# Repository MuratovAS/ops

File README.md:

# ops
Open pocket switch

Very raw work is stored here. Don't use it!
Everything needs to be redone.
Problems:
- routes are not coordinated
- technological standards are not observed

https://wiki.pine64.org/wiki/Clusterboard
https://github.com/libc0607/Realtek_switch_hacking/tree/files

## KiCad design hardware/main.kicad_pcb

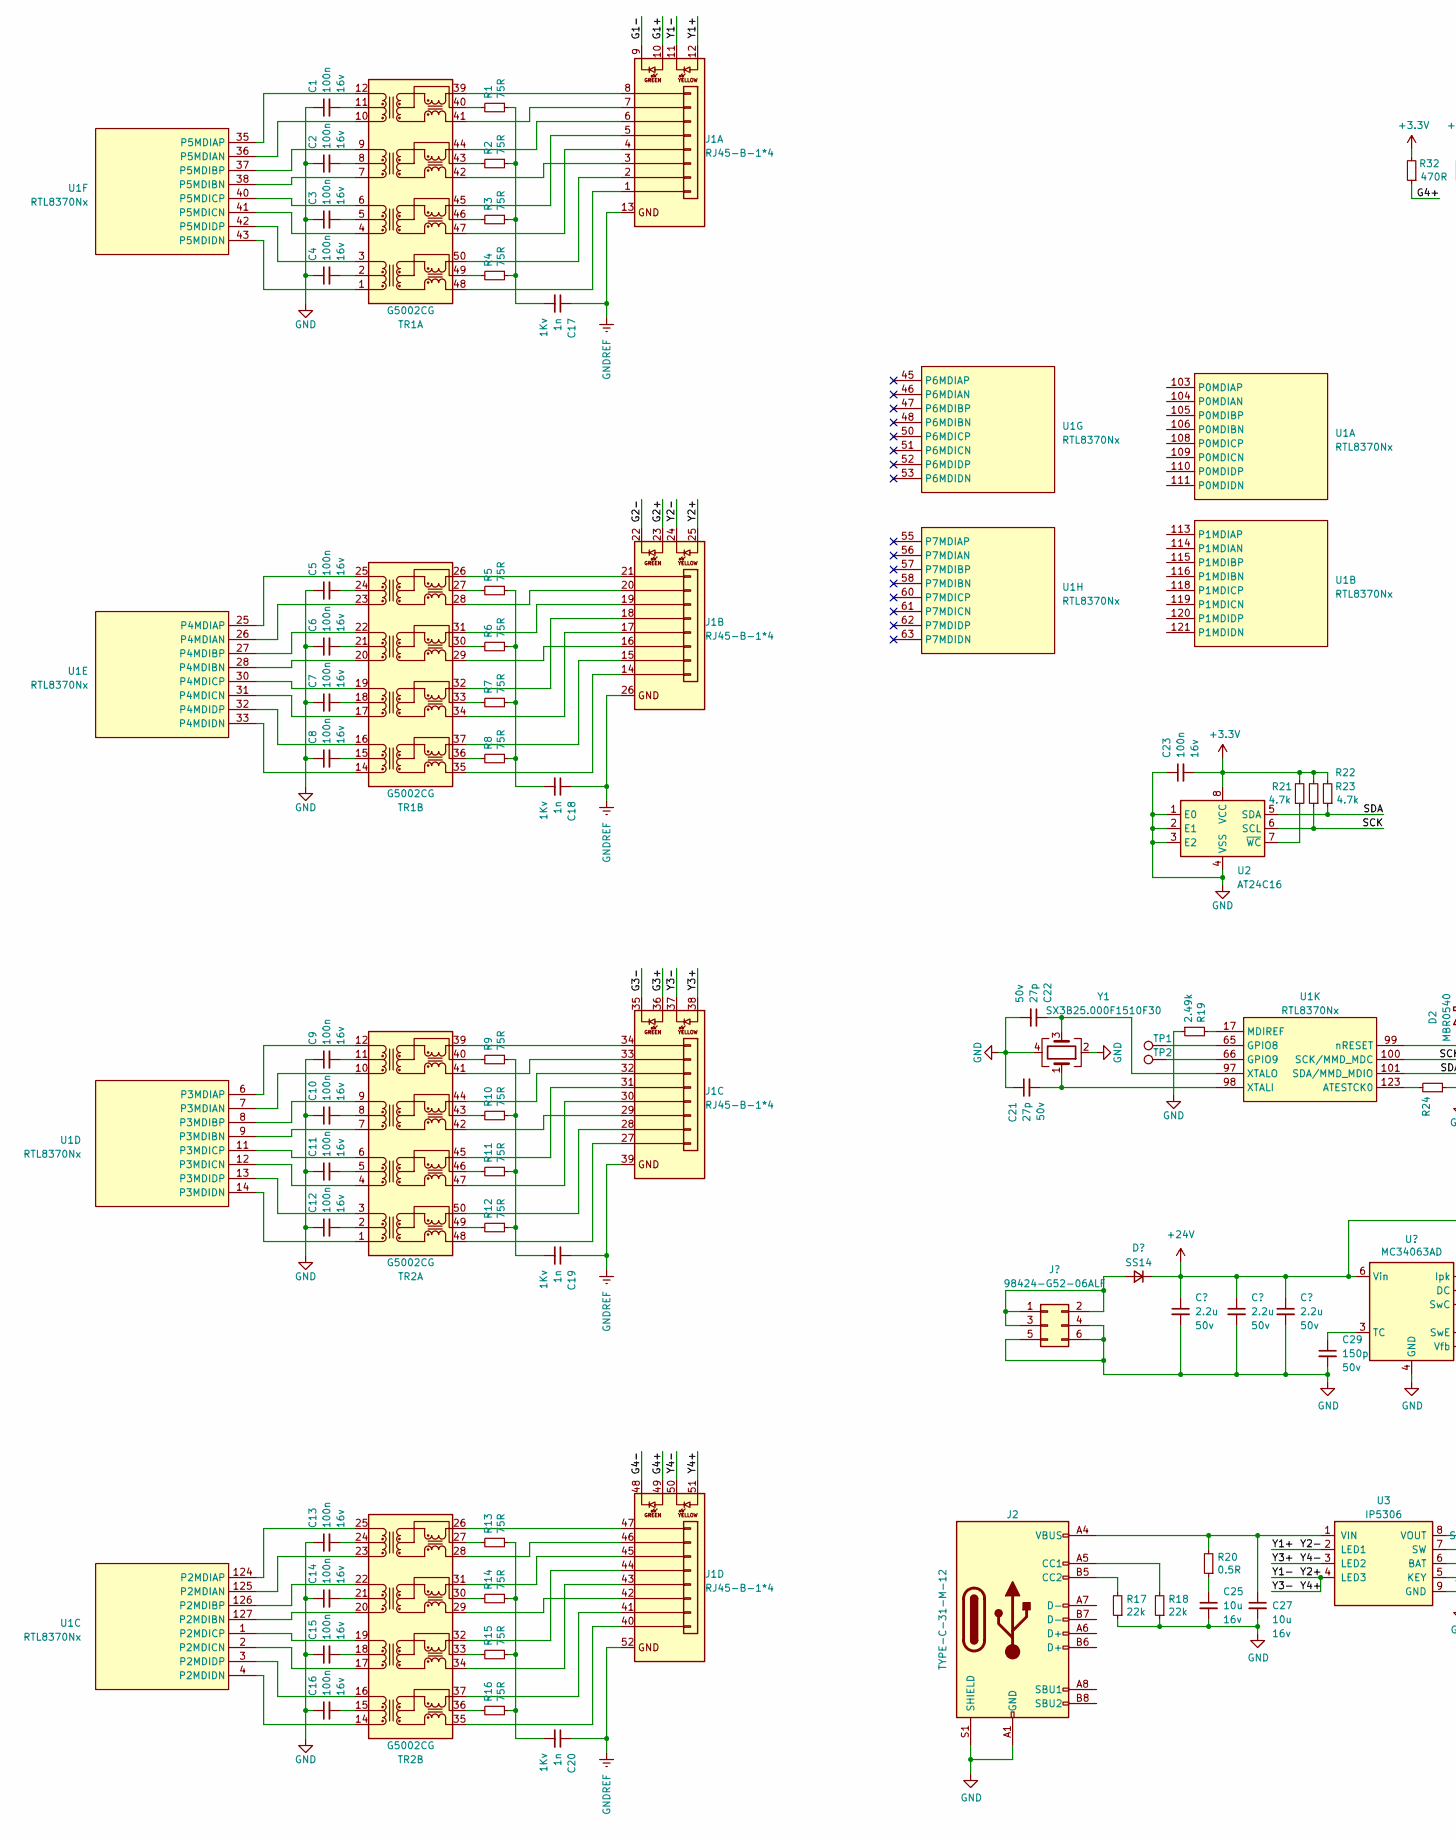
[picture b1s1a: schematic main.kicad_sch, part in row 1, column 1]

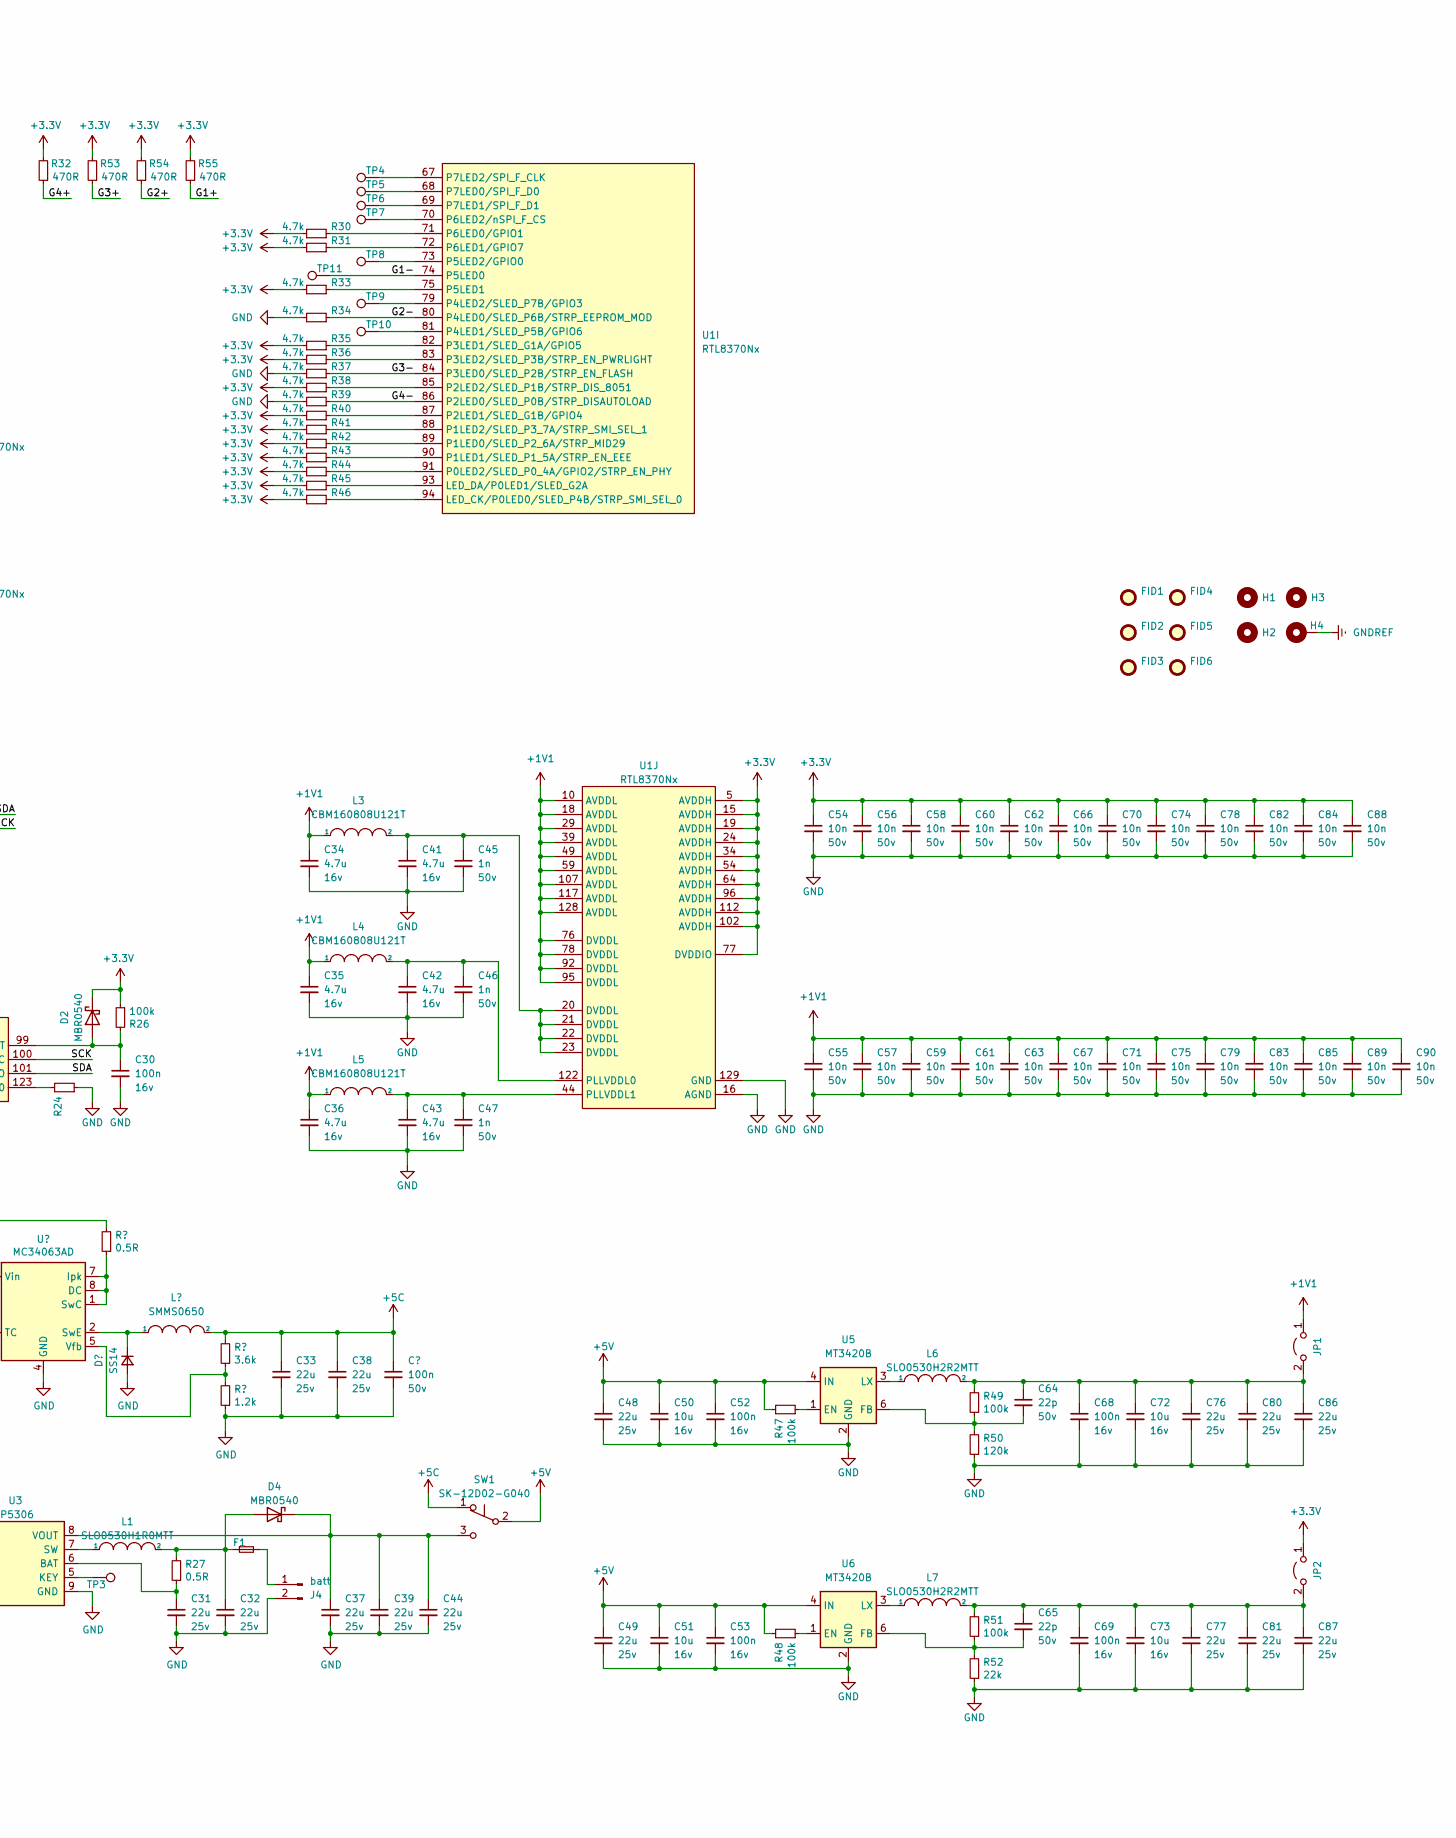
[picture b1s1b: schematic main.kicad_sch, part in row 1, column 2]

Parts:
C1, C2, C3, C4, C5, C6, C7, C8, C9, C10, C11, C12, C13, C14, C15, C16, C23, C30, C52, C53, C68, C69: 100n; C_0402_1005Metric; Voltage 16v; lcsc C1525
C17, C18, C19, C20: 1n; C_0805_2012Metric; Voltage 1Kv; lcsc C303890
C21, C22: 27p; C_0402_1005Metric; Voltage 50v; lcsc C1557
C24, C26, C28: 2.2u; C_1206_3216Metric; Voltage 50v; lcsc C50254
C25, C27, C50, C51, C72, C73: 10u; C_0805_2012Metric; Voltage 16v; lcsc C95841
C29: 150p; C_0603_1608Metric; Voltage 50v; lcsc C1594
C31, C32, C33, C37, C38, C39, C44, C48, C49, C76, C77, C80, C81, C86, C87: 22u; C_0805_2012Metric; Voltage 25v; lcsc C45783
C34, C35, C36, C41, C42, C43: 4.7u; C_0805_2012Metric; Voltage 16v; lcsc C1779
C40: 100n; C_0805_2012Metric; Voltage 50v; lcsc C49678
C45, C46, C47: 1n; C_0402_1005Metric; Voltage 50v; lcsc C1523
C54, C55, C56, C57, C58, C59, C60, C61, C62, C63, C66, C67, C70, C71, C74, C75, C78, C79, C82, C83, C84, C85, C88, C89, C90: 10n; C_0402_1005Metric; Voltage 50v; lcsc C15195
C64, C65: 22p; C_0603_1608Metric; Voltage 50v; lcsc C1653
D1, D3: SS14; D_SMA; lcsc C2480
D2, D4: MBR0540; D_SOD-123; lcsc C116159
F1: 0466001.NRHF; Fuse_1812_4532Metric; lcsc C151135
FID1, FID2, FID3, FID4, FID5, FID6: F; Fiducial_1mm_Mask3mm
H1, H2, H3, H4: H; MountingHole_3.2mm_M3_DIN965_Pad
J1: RJ45-B-1*4; RJ45_B_1_4; lcsc C138390
J2: TYPE-C-31-M-12; USB_C_Receptacle_HRO_TYPE-C-31-M-12; lcsc C165948
J3: 98424-G52-06ALF; PinSocket_2x03_P2.00mm_Vertical_SMD; lcsc C180222
J4: batt; PinHeader_1x02_P2.54mm_Vertical; lcsc C492401
JP1, JP2: jump; SolderJumper-2_P1.3mm_Open_Pad1.0x1.5mm
L1: SLO0530H1R0MTT; Power_inductor_SMD_0530; lcsc C325960
L2: SMMS0650; SMDL_7.1x6.6x5mm; lcsc C2894722
L3, L4, L5: CBM160808U121T; L_0603_1608Metric; lcsc C62708
L6, L7: SLO0530H2R2MTT; Power_inductor_SMD_0530; lcsc C325962
R1, R2, R3, R4, R5, R6, R7, R8, R9, R10, R11, R12, R13, R14, R15, R16: 75R; R_0402_1005Metric; lcsc C25133
R17, R18, R52: 22k; R_0402_1005Metric; lcsc C25768
R19: 2.49k; R_0402_1005Metric; lcsc C145071
R20, R27: 0.5R; R_0603_1608Metric; lcsc C149626
R21, R22, R23, R30, R31, R33, R34, R35, R36, R37, R38, R39, R40, R41, R42, R43, R44, R45, R46: 4.7k; R_0402_1005Metric; lcsc C25900
R24: R_0402_1005Metric
R25: 0.5R; R_0805_2012Metric; lcsc C912543
R26, R47, R48, R49, R51: 100k; R_0402_1005Metric; lcsc C25741
R28: 3.6k; R_0603_1608Metric; lcsc C22980
R29: 1.2k; R_0603_1608Metric; lcsc C22765
R32, R53, R54, R55: 470R; R_0402_1005Metric; lcsc C25117
R50: 120k; R_0603_1608Metric; lcsc C25808
SW1: SK-12D02-G040; SW_Slide_SK-12D02-G040; lcsc C2930976
TP1, TP2, TP3, TP4, TP5, TP6, TP7, TP8, TP9, TP10, TP11: TestPoint; TestPoint_Pad_D0.5mm
TR1, TR2: G5002CG; Transformer_Ethernet_YDS-Tech_G5002CG; lcsc C2904718
U1: RTL8370Nx; LQFP-128_14x20mm_P0.5mm; lcsc C2803243
U2: AT24C16; SOIC-8_3.9x4.9mm_P1.27mm; lcsc C561263
U3: IP5306; SOIC-8-1EP_3.9x4.9mm_P1.27mm_EP2.29x3mm; lcsc C181692
U4: MC34063AD; SOIC-8_3.9x4.9mm_P1.27mm; lcsc C32078
U5, U6: MT3420B; SOT-23-6; lcsc C88169
Y1: SX3B25.000F1510F30; Oscillator_SMD_SMD3225-4P; lcsc C2901686

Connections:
+1V1: C34.1, C35.1, C36.1, C55.1, C57.1, C59.1, C61.1, C63.1, C67.1, C71.1, C75.1, C79.1, C83.1, C85.1, C89.1, C90.1, JP1.1 (A), L3.1, L4.1, L5.1, U1.10 (AVDDL), U1.18 (AVDDL), U1.29 (AVDDL), U1.39 (AVDDL), U1.49 (AVDDL), U1.59 (AVDDL), U1.76 (DVDDL), U1.78 (DVDDL), U1.92 (DVDDL), U1.95 (DVDDL), U1.107 (AVDDL), U1.117 (AVDDL), U1.128 (AVDDL)
+3V3: C23.2, C54.1, C56.1, C58.1, C60.1, C62.1, C66.1, C70.1, C74.1, C78.1, C82.1, C84.1, C88.1, D2.1 (K), JP2.1 (A), R21.2, R22.2, R23.2, R26.1, R30.2, R31.2, R32.2, R33.2, R35.2, R36.2, R38.2, R40.2, R41.2, R42.2, R43.2, R44.2, R45.2, R46.2, R53.2, R54.2, R55.2, U1.5 (AVDDH), U1.15 (AVDDH), U1.19 (AVDDH), U1.24 (AVDDH), U1.34 (AVDDH), U1.54 (AVDDH), U1.64 (AVDDH), U1.77 (DVDDIO), U1.96 (AVDDH), U1.102 (AVDDH), U1.112 (AVDDH), U2.8 (VCC)
+5C: C33.1, C38.1, C40.1, L2.2, R28.2, SW1.1 (A)
+5V: C48.1, C49.1, C50.1, C51.1, C52.1, C53.1, R47.2, R48.2, SW1.2 (B), U5.4 (IN), U6.4 (IN)
+24V: C24.1, C26.1, C28.1, D1.1 (K), R25.2, U4.6 (Vin)
/G1+: J1.10, R55.1
/G1-: J1.9, TP11.1, U1.74 (P5LED0)
/G2+: J1.23, R54.1
/G2-: J1.22, R34.1, U1.80 (P4LED0/SLED_P6B/STRP_EEPROM_MOD)
/G3+: J1.36, R53.1
/G3-: J1.35, R37.1, U1.84 (P3LED0/SLED_P2B/STRP_EN_FLASH)
/G4+: J1.49, R32.1
/G4-: J1.48, R39.1, U1.86 (P2LED0/SLED_P0B/STRP_DISAUTOLOAD)
/SCK: R22.1, U1.100 (SCK/MMD_MDC), U2.6 (SCL)
/SDA: R23.1, U1.101 (SDA/MMD_MDIO), U2.5 (SDA)
/Y1+: J1.12, J1.24, U3.2 (LED1)
/Y1-: J1.11, J1.25, J1.37, J1.51, U3.4 (LED3)
/Y3+: J1.38, J1.50, U3.3 (LED2)
GND: C1.1, C2.1, C3.1, C4.1, C5.1, C6.1, C7.1, C8.1, C9.1, C10.1, C11.1, C12.1, C13.1, C14.1, C15.1, C16.1, C21.1, C22.2, C23.1, C24.2, C25.2, C26.2, C27.2, C28.2, C29.2, C30.2, C31.2, C32.2, C33.2, C34.2, C35.2, C36.2, C37.2, C38.2, C39.2, C40.2, C41.2, C42.2, C43.2, C44.2, C45.2, C46.2, C47.2, C48.2, C49.2, C50.2, C51.2, C52.2, C53.2, C54.2, C55.2, C56.2, C57.2, C58.2, C59.2, C60.2, C61.2, C62.2, C63.2, C66.2, C67.2, C68.2, C69.2, C70.2, C71.2, C72.2, C73.2, C74.2, C75.2, C76.2, C77.2, C78.2, C79.2, C80.2, C81.2, C82.2, C83.2, C84.2, C85.2, C86.2, C87.2, C88.2, C89.2, C90.2, D3.2 (A), J2.A1 (GND), J2.A12 (GND), J2.B1 (GND), J2.B12 (GND), J2.S1 (SHIELD), J3.4, J3.5, J3.6, J4.2, R17.1, R18.1, R19.1, R24.1, R29.1, R34.2, R37.2, R39.2, R50.1, R52.1, U1.16 (AGND), U1.129 (GND), U2.1 (E0), U2.2 (E1), U2.3 (E2), U2.4 (VSS), U3.9 (GND), U4.4 (GND), U5.2 (GND), U6.2 (GND), Y1.2, Y1.4
GNDREF: C17.1, C18.1, C19.1, C20.1, H4.1, J1.13, J1.26, J1.39, J1.52
unnamed: C17.2, R1.1, R2.1, R3.1, R4.1
unnamed: C18.2, R5.1, R6.1, R7.1, R8.1
unnamed: C19.2, R9.1, R10.1, R11.1, R12.1
unnamed: C20.2, R13.1, R14.1, R15.1, R16.1
unnamed: C25.1, R20.1
unnamed: C41.1, C45.1, L3.2, U1.20 (DVDDL), U1.21 (DVDDL), U1.22 (DVDDL), U1.23 (DVDDL)
unnamed: D1.2 (A), J3.1, J3.2, J3.3
unnamed: C30.1, D2.2 (A), R26.2, U1.99 (nRESET)
unnamed: D3.1 (K), L2.1, U4.2 (SwE)
unnamed: C32.1, D4.2 (A), F1.1, L1.2, R27.2
unnamed: C37.1, C39.1, C44.1, D4.1 (K), SW1.3 (C), U3.8 (VOUT)
unnamed: J1.1 (BI_DA+), TR1.48 (MX1+)
unnamed: J1.2 (BI_DA-), TR1.50 (MX1-)
unnamed: J1.3 (BI_DB+), TR1.42 (MX3+)
unnamed: J1.6 (BI_DB-), TR1.44 (MX3-)
unnamed: J1.4 (BI_DC+), TR1.47 (MX2+)
unnamed: J1.5 (BI_DC-), TR1.45 (MX2-)
unnamed: J1.7 (BI_DD+), TR1.41 (MX4+)
unnamed: J1.8 (BI_DD-), TR1.39 (MX4-)
unnamed: J1.14 (BI_DA+), TR1.35 (MX1+)
unnamed: J1.15 (BI_DA-), TR1.37 (MX1-)
unnamed: J1.16 (BI_DB+), TR1.29 (MX3+)
unnamed: J1.19 (BI_DB-), TR1.31 (MX3-)
unnamed: J1.17 (BI_DC+), TR1.34 (MX2+)
unnamed: J1.18 (BI_DC-), TR1.32 (MX2-)
unnamed: J1.20 (BI_DD+), TR1.28 (MX4+)
unnamed: J1.21 (BI_DD-), TR1.26 (MX4-)
unnamed: J1.27 (BI_DA+), TR2.48 (MX1+)
unnamed: J1.28 (BI_DA-), TR2.50 (MX1-)
unnamed: J1.29 (BI_DB+), TR2.42 (MX3+)
unnamed: J1.32 (BI_DB-), TR2.44 (MX3-)
unnamed: J1.30 (BI_DC+), TR2.47 (MX2+)
unnamed: J1.31 (BI_DC-), TR2.45 (MX2-)
unnamed: J1.33 (BI_DD+), TR2.41 (MX4+)
unnamed: J1.34 (BI_DD-), TR2.39 (MX4-)
unnamed: J1.40 (BI_DA+), TR2.35 (MX1+)
unnamed: J1.41 (BI_DA-), TR2.37 (MX1-)
unnamed: J1.42 (BI_DB+), TR2.29 (MX3+)
unnamed: J1.45 (BI_DB-), TR2.31 (MX3-)
unnamed: J1.43 (BI_DC+), TR2.34 (MX2+)
unnamed: J1.44 (BI_DC-), TR2.32 (MX2-)
unnamed: J1.46 (BI_DD+), TR2.28 (MX4+)
unnamed: J1.47 (BI_DD-), TR2.26 (MX4-)
unnamed: J2.A5 (CC1), R18.2
unnamed: J2.B5 (CC2), R17.2
unnamed: F1.2, J4.1
unnamed: C64.1, C68.1, C72.1, C76.1, C80.1, C86.1, JP1.2 (B), L6.2, R49.2
unnamed: C65.1, C69.1, C73.1, C77.1, C81.1, C87.1, JP2.2 (B), L7.2, R51.2
unnamed: R4.2, TR1.49 (CMT1)
unnamed: R3.2, TR1.46 (CMT2)
unnamed: R2.2, TR1.43 (CMT3)
unnamed: R1.2, TR1.40 (CMT4)
unnamed: C4.2, TR1.2 (TCT1)
unnamed: C3.2, TR1.5 (TCT2)
unnamed: C2.2, TR1.8 (TCT3)
unnamed: C1.2, TR1.11 (TCT4)
unnamed: TR1.1 (TD1+), U1.43 (P5MDIDN)
unnamed: TR1.3 (TD1-), U1.42 (P5MDIDP)
unnamed: TR1.4 (TD2+), U1.41 (P5MDICN)
unnamed: TR1.6 (TD2-), U1.40 (P5MDICP)
unnamed: TR1.7 (TD3+), U1.38 (P5MDIBN)
unnamed: TR1.9 (TD3-), U1.37 (P5MDIBP)
unnamed: TR1.10 (TD4+), U1.36 (P5MDIAN)
unnamed: TR1.12 (TD4-), U1.35 (P5MDIAP)
unnamed: R8.2, TR1.36 (CMT1)
unnamed: R7.2, TR1.33 (CMT2)
unnamed: R6.2, TR1.30 (CMT3)
unnamed: R5.2, TR1.27 (CMT4)
unnamed: C8.2, TR1.15 (TCT1)
unnamed: C7.2, TR1.18 (TCT2)
unnamed: C6.2, TR1.21 (TCT3)
unnamed: C5.2, TR1.24 (TCT4)
unnamed: TR1.14 (TD1+), U1.33 (P4MDIDN)
unnamed: TR1.16 (TD1-), U1.32 (P4MDIDP)
unnamed: TR1.17 (TD2+), U1.31 (P4MDICN)
unnamed: TR1.19 (TD2-), U1.30 (P4MDICP)
unnamed: TR1.20 (TD3+), U1.28 (P4MDIBN)
unnamed: TR1.22 (TD3-), U1.27 (P4MDIBP)
unnamed: TR1.23 (TD4+), U1.26 (P4MDIAN)
unnamed: TR1.25 (TD4-), U1.25 (P4MDIAP)
unnamed: R12.2, TR2.49 (CMT1)
unnamed: R11.2, TR2.46 (CMT2)
unnamed: R10.2, TR2.43 (CMT3)
unnamed: R9.2, TR2.40 (CMT4)
unnamed: C12.2, TR2.2 (TCT1)
unnamed: C11.2, TR2.5 (TCT2)
unnamed: C10.2, TR2.8 (TCT3)
unnamed: C9.2, TR2.11 (TCT4)
unnamed: TR2.1 (TD1+), U1.14 (P3MDIDN)
unnamed: TR2.3 (TD1-), U1.13 (P3MDIDP)
unnamed: TR2.4 (TD2+), U1.12 (P3MDICN)
unnamed: TR2.6 (TD2-), U1.11 (P3MDICP)
unnamed: TR2.7 (TD3+), U1.9 (P3MDIBN)
unnamed: TR2.9 (TD3-), U1.8 (P3MDIBP)
unnamed: TR2.10 (TD4+), U1.7 (P3MDIAN)
unnamed: TR2.12 (TD4-), U1.6 (P3MDIAP)
unnamed: R16.2, TR2.36 (CMT1)
unnamed: R15.2, TR2.33 (CMT2)
unnamed: R14.2, TR2.30 (CMT3)
unnamed: R13.2, TR2.27 (CMT4)
unnamed: C16.2, TR2.15 (TCT1)
unnamed: C15.2, TR2.18 (TCT2)
unnamed: C14.2, TR2.21 (TCT3)
unnamed: C13.2, TR2.24 (TCT4)
unnamed: TR2.14 (TD1+), U1.4 (P2MDIDN)
unnamed: TR2.16 (TD1-), U1.3 (P2MDIDP)
unnamed: TR2.17 (TD2+), U1.2 (P2MDICN)
unnamed: TR2.19 (TD2-), U1.1 (P2MDICP)
unnamed: TR2.20 (TD3+), U1.127 (P2MDIBN)
unnamed: TR2.22 (TD3-), U1.126 (P2MDIBP)
unnamed: TR2.23 (TD4+), U1.125 (P2MDIAN)
unnamed: TR2.25 (TD4-), U1.124 (P2MDIAP)
unnamed: R46.1, U1.94 (LED_CK/P0LED0/SLED_P4B/STRP_SMI_SEL_0)
unnamed: R45.1, U1.93 (LED_DA/P0LED1/SLED_G2A)
unnamed: R44.1, U1.91 (P0LED2/SLED_P0_4A/GPIO2/STRP_EN_PHY)
unnamed: R42.1, U1.89 (P1LED0/SLED_P2_6A/STRP_MID29)
unnamed: R43.1, U1.90 (P1LED1/SLED_P1_5A/STRP_EN_EEE)
unnamed: R41.1, U1.88 (P1LED2/SLED_P3_7A/STRP_SMI_SEL_1)
unnamed: R40.1, U1.87 (P2LED1/SLED_G1B/GPIO4)
unnamed: R38.1, U1.85 (P2LED2/SLED_P1B/STRP_DIS_8051)
unnamed: R35.1, U1.82 (P3LED1/SLED_G1A/GPIO5)
unnamed: R36.1, U1.83 (P3LED2/SLED_P3B/STRP_EN_PWRLIGHT)
unnamed: TP10.1, U1.81 (P4LED1/SLED_P5B/GPIO6)
unnamed: TP9.1, U1.79 (P4LED2/SLED_P7B/GPIO3)
unnamed: R33.1, U1.75 (P5LED1)
unnamed: TP8.1, U1.73 (P5LED2/GPIO0)
unnamed: R30.1, U1.71 (P6LED0/GPIO1)
unnamed: R31.1, U1.72 (P6LED1/GPIO7)
unnamed: TP7.1, U1.70 (P6LED2/nSPI_F_CS)
unnamed: TP5.1, U1.68 (P7LED0/SPI_F_D0)
unnamed: TP6.1, U1.69 (P7LED1/SPI_F_D1)
unnamed: TP4.1, U1.67 (P7LED2/SPI_F_CLK)
unnamed: C42.1, C46.1, L4.2, U1.122 (PLLVDDL0)
unnamed: C43.1, C47.1, L5.2, U1.44 (PLLVDDL1)
unnamed: R24.2, U1.123 (ATESTCK0)
unnamed: TP1.1, U1.65 (GPIO8)
unnamed: TP2.1, U1.66 (GPIO9)
unnamed: R19.2, U1.17 (MDIREF)
unnamed: C21.2, U1.98 (XTALI), Y1.1
unnamed: C22.1, U1.97 (XTALO), Y1.3
unnamed: R21.1, U2.7 (~WC)
unnamed: C31.1, R27.1, U3.6 (BAT)
unnamed: TP3.1, U3.5 (KEY)
unnamed: L1.1, U3.7 (SW)
unnamed: C27.1, J2.A4 (VBUS), J2.A9 (VBUS), J2.B4 (VBUS), J2.B9 (VBUS), R20.2, U3.1 (VIN)
unnamed: R25.1, U4.1 (SwC), U4.7 (Ipk), U4.8 (DC)
unnamed: C29.1, U4.3 (TC)
unnamed: R28.1, R29.2, U4.5 (Vfb)
unnamed: R47.1, U5.1 (EN)
unnamed: C64.2, R49.1, R50.2, U5.6 (FB)
unnamed: L6.1, U5.3 (LX)
unnamed: R48.1, U6.1 (EN)
unnamed: C65.2, R51.1, R52.2, U6.6 (FB)
unnamed: L7.1, U6.3 (LX)

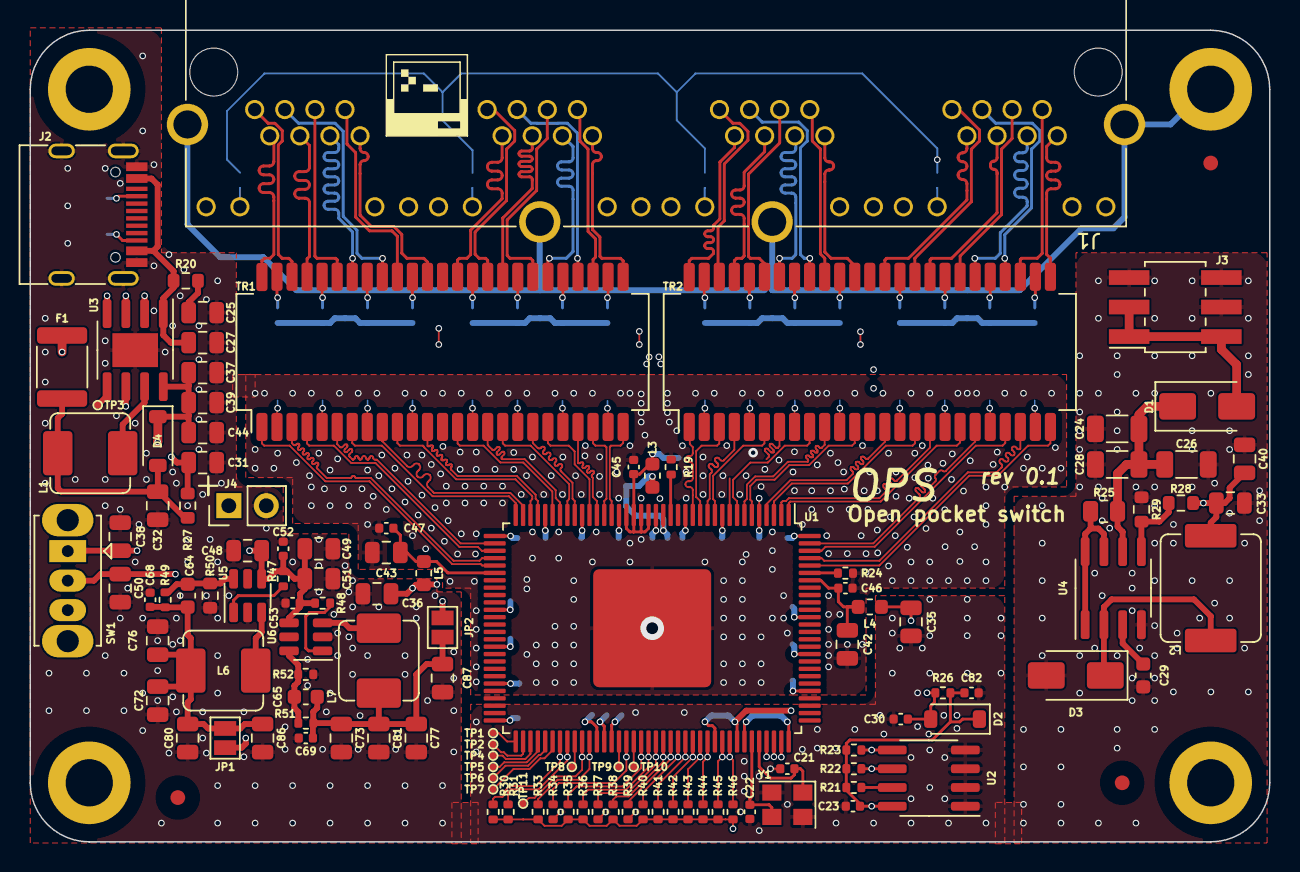
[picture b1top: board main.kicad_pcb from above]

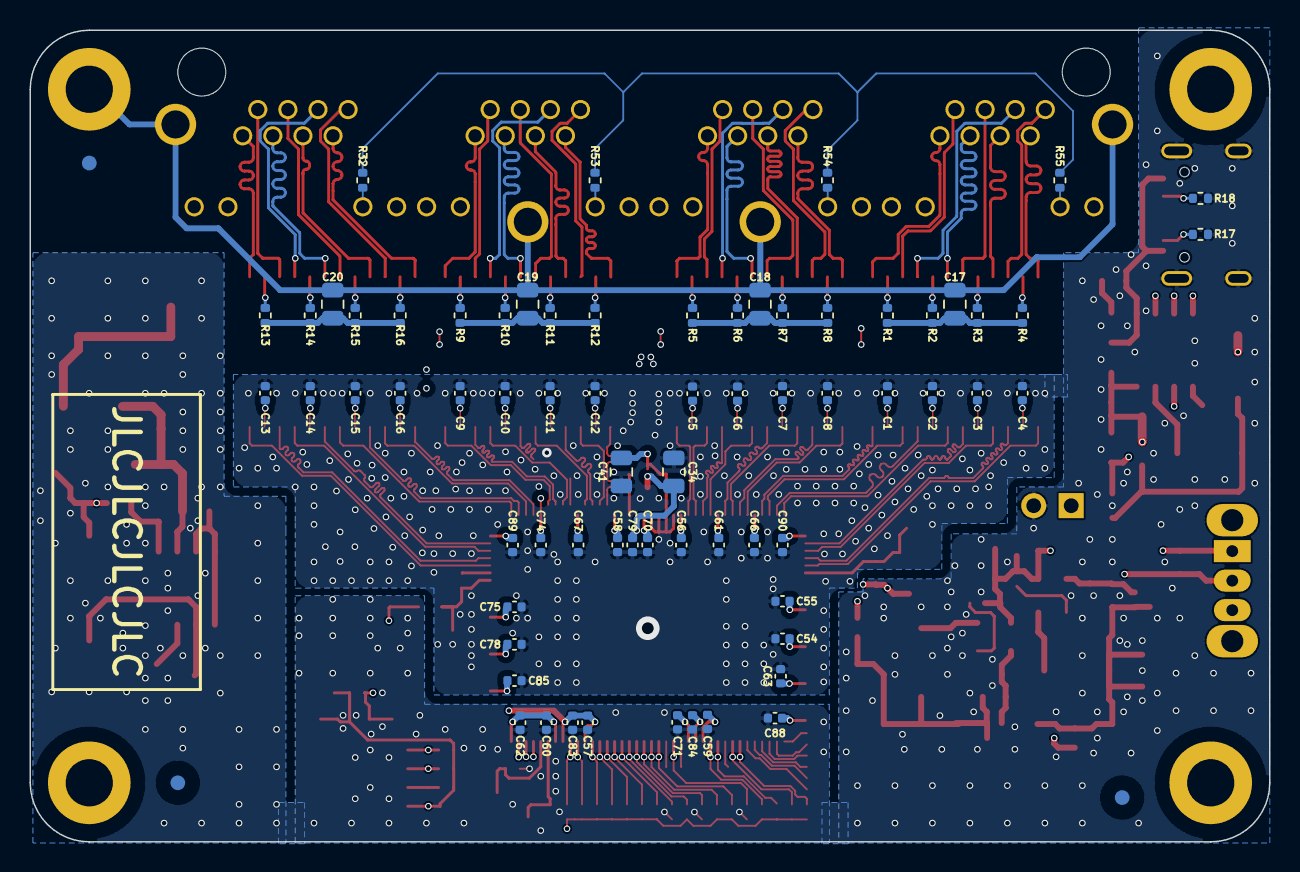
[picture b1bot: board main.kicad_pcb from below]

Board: 4 copper layers, 84.0 x 55.0 mm, 194 parts (71 on the bottom side), 174 nets.

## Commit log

2023-04-22 init sch
2023-04-22 init pcb
2023-04-23 The layout of the board
2023-04-24 update sch and pcb
2023-04-24 update pcb rules
2023-04-27 update pcb
2023-04-28 finished with tracing
2023-04-28 update silk
2023-04-28 add vias
2023-05-02 fix wire
2023-05-03 fix pcb and check drc
2023-06-03 completion of development.
